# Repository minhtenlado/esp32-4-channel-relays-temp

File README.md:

<div align="center">

# ESP32-C3 MINI

### Bo mạch điều khiển IoT Wi-Fi & Bluetooth LE · 4 kênh relay · Cảm biến SHT31

**Bo mạch PCB 2 lớp được thiết kế bằng KiCad, tích hợp ESP32-C3, 4 ngõ ra relay, cảm biến nhiệt độ/độ ẩm SHT31, cổng USB Type-C và đầu mở rộng GPIO/UART.**

**[Giới thiệu](#-giới-thiệu) · [Hình ảnh PCB](#-hình-ảnh-pcb) · [Phần cứng](#-kiến-trúc-phần-cứng) · [Sơ đồ chân](#-bảng-phân-bổ-chân) · [Cấu trúc dự án](#-cấu-trúc-thư-mục) · [Hướng dẫn sử dụng](#-hướng-dẫn-sử-dụng)**

</div>

---

## 📖 Giới thiệu

**ESP32-C3 MINI** là bo mạch điều khiển IoT được thiết kế riêng, phục vụ các ứng dụng điều khiển thiết bị và giám sát môi trường. Trung tâm hệ thống là mô-đun **ESP32-C3-WROOM-02**, kết hợp **4 relay chuyển mạch SPDT** và cảm biến nhiệt độ, độ ẩm **Sensirion SHT31-DIS**.

Thiết kế phù hợp để phát triển các ứng dụng tự động hóa sử dụng Wi-Fi, thu thập dữ liệu cảm biến và điều khiển tải thông qua relay. Repository này tập trung vào **thiết kế phần cứng, PCB và các tệp phục vụ sản xuất**; chưa bao gồm mã nguồn firmware ứng dụng trong bộ dữ liệu đã cung cấp.

### ✨ Tính năng nổi bật

- **ESP32-C3-WROOM-02:** hỗ trợ Wi-Fi 2,4 GHz và Bluetooth Low Energy (BLE).
- **4 kênh relay SPDT:** mỗi kênh sử dụng PC817 và transistor MMBT3904 để điều khiển cuộn relay.
- **Đầu nối NO / COM / NC:** mỗi relay có một terminal 3 chân để đấu nối tải.
- **SHT31-DIS:** cảm biến đo nhiệt độ và độ ẩm, giao tiếp I²C.
- **USB Type-C:** cấp nguồn 5 V và kết nối các đường dữ liệu USB tích hợp trên ESP32-C3.
- **Hai nút BOOT và RESET:** hỗ trợ khởi động, nạp chương trình và kiểm thử.
- **Đầu mở rộng 2 × 4 chân:** đưa ra UART, GPIO0, GPIO1, nguồn 3,3 V, nguồn 5 V và GND.
- **Các linh kiện bảo vệ:** cầu chì đầu vào, linh kiện bảo vệ ESD USB, diode dập xung ngược cho cuộn relay và vị trí lắp MOV ở phía tiếp điểm.
- **PCB 2 lớp:** bố trí linh kiện SMD/THT, có hình ảnh mô phỏng 3D và vùng dành riêng cho anten Wi-Fi.
---

## 🖼️ Hình ảnh PCB

### Mô hình 3D

| Góc nhìn 3D số 1 | Góc nhìn 3D số 2 |
| :---: | :---: |
|  |  |

### Bố trí linh kiện và các lớp đồng

| Tổng quan các lớp PCB | Bố trí footprint |
| :---: | :---: |
|  |  |

| Lớp đồng mặt trước — F.Cu | Lớp đồng mặt sau — B.Cu |
| :---: | :---: |
|  |  |

---

## 🧩 Kiến trúc phần cứng

### System Block Diagram

```mermaid
flowchart TB
    USB["USB Type-C / 5 V Input"] --> PWR["F1 Fuse + SS14 Diode + 5 V Power Rail"]
    PWR --> LDO["AMS1117-3.3 Voltage Regulator"]
    LDO --> ESP["ESP32-C3-WROOM-02"]
    PWR --> RELAYPOWER["Relay Coil Power Supply"]
    USB <-->|"USB D+ / D−"| ESP
    ESP <-->|"I²C: SDA / SCL"| SHT["SHT31-DIS Temperature & Humidity Sensor"]
    ESP <-->|"UART + GPIO"| HDR["2 × 4 Expansion Header"]
    ESP --> DRV["4 × PC817 + MMBT3904 Relay Drivers"]
    DRV --> COILS["4 Relay Coils"]
    RELAYPOWER --> COILS
    COILS -. "Mechanical Actuation" .-> CONTACTS["4 × NO / COM / NC Output Terminals"]
    MOV["MOV Surge Protection"] --- CONTACTS
```

### Thông số kỹ thuật

| Thông số | Giá trị / thiết kế |
|---|---|
| Tên dự án | `ESP32_C3_MINI` |
| Vi điều khiển / mô-đun | Espressif `ESP32-C3-WROOM-02` |
| Kết nối không dây | Wi-Fi 2,4 GHz, Bluetooth LE (khả năng của mô-đun) |
| Số lớp PCB | 2 lớp đồng: `F.Cu` và `B.Cu` |
| Độ dày PCB khai báo | 1,6 mm |
| Kích thước bo mạch tham chiếu | Khoảng 88 × 89,5 mm theo file PCB được cung cấp |
| Nguồn đầu vào chính | USB Type-C, 5 V danh định |
| Nguồn logic | 3,3 V qua `AMS1117-3.3` |
| Số kênh relay | 4 kênh SPDT, footprint kiểu SANYOU SRD |
| Mạch kích relay | 4 × `PC817` và 4 × `MMBT3904` |
| Linh kiện bảo vệ relay | 4 × `1N4007` và 4 × MOV `07D471K` trong thiết kế |
| Cảm biến | `SHT31-DIS`, giao tiếp I²C |
| Giao tiếp nạp / phát triển | USB tích hợp ESP32-C3 và UART tại đầu mở rộng |
| Nút điều khiển | BOOT (`S1`), RESET (`S2`) |
| Đầu nối mở rộng | Header 2 × 4, bước chân 2,54 mm (`J5`) |
| Công cụ thiết kế | KiCad |

---

## 🔌 Bảng phân bổ chân

### GPIO trên ESP32-C3

| Chức năng | Chân ESP32-C3 | Tên tín hiệu / ghi chú |
|---|---|---|
| Điều khiển relay 1 | `GPIO3` | `RL1` |
| Điều khiển relay 2 | `GPIO4` | `RL2` |
| Điều khiển relay 3 | `GPIO5` | `RL3` |
| Điều khiển relay 4 | `GPIO6` | `RL4` |
| SHT31 SDA | `GPIO7` | `SDA` |
| SHT31 SCL | `GPIO10` | `SCL` |
| USB D− | `GPIO18` | `D-` |
| USB D+ | `GPIO19` | `D+` |
| UART RX | `GPIO20` | `RX` |
| UART TX | `GPIO21` | `TX` |
| Nút BOOT | `GPIO9` | `IO9` |
| GPIO mở rộng | `GPIO0` | `IO0` |
| GPIO mở rộng | `GPIO1` | `IO1` |

> **Lưu ý chân khởi động:** GPIO2, GPIO8 và GPIO9 là các chân *strapping* của ESP32-C3. Không được thiết kế mạch ngoại vi làm thay đổi trạng thái khởi động ngoài ý muốn.

### Đầu nối mở rộng J5

| Chân | Tín hiệu | Chân | Tín hiệu |
|:---:|---|:---:|---|
| 1 | GPIO0 (`IO0`) | 2 | GND |
| 3 | GPIO1 (`IO1`) | 4 | GND |
| 5 | UART RX (`GPIO20`) | 6 | +3,3 V |
| 7 | UART TX (`GPIO21`) | 8 | +5 V |

> [!WARNING]
> Chân GPIO ESP32-C3 sử dụng logic **3,3 V**, không được đưa trực tiếp tín hiệu 5 V vào GPIO. Kiểm tra chiều đánh số chân header và khả năng cấp dòng của nguồn trước khi kết nối mô-đun bên ngoài.

### Cảm biến nhiệt độ / độ ẩm SHT31

| Chức năng | Kết nối |
|---|---|
| SDA | GPIO7 |
| SCL | GPIO10 |
| Điện trở kéo lên SDA/SCL | 4,7 kΩ lên 3,3 V (`R25`, `R26`) |
| Địa chỉ I²C | `0x44` theo cấu hình ADDR ở mức thấp trong sơ đồ đã gửi |
| Nguồn | 3,3 V |

### Các kênh relay

| Kênh | Ký hiệu relay | Terminal đầu ra | Tiếp điểm |
|:---:|---|---|---|
| 1 | `K1` | `J1` | NO · COM · NC |
| 2 | `K2` | `J2` | NO · COM · NC |
| 3 | `K3` | `J3` | NO · COM · NC |
| 4 | `K4` | `J4` | NO · COM · NC |

Theo cách bố trí mạch kích trong sơ đồ đã cung cấp, GPIO mức **HIGH** để kích relay.
---

## ⚡ Nguồn cấp và bảo vệ

### Khối nguồn

Nguồn **5 V từ USB Type-C** đi qua cầu chì `F1` và diode Schottky `D1 (SS14)` tới đường nguồn 5 V của mạch. IC `AMS1117-3.3` tạo ra nguồn **3,3 V** cho khối ESP32-C3 và các phần tử logic.

Mạch có linh kiện `PRTR5V0U2X` hỗ trợ bảo vệ chống phóng tĩnh điện (ESD) trên đường USB.

### Khối điều khiển relay

Mỗi kênh gồm các thành phần chính:

1. Tín hiệu GPIO từ ESP32-C3.
2. Optocoupler `PC817`.
3. Transistor `MMBT3904` điều khiển cuộn relay.
4. Diode `1N4007` dập xung điện áp ngược khi ngắt cuộn dây.
5. LED hiển thị trạng thái và mạng điện trở đi kèm.
6. Terminal đấu nối tải với ba tiếp điểm NO, COM và NC.

Thiết kế có thêm bốn vị trí MOV `RV1`–`RV4` ở khu vực tiếp điểm relay.

> [!CAUTION]
> **An toàn điện:** PCB và file Gerber không phải chứng nhận an toàn điện. Nếu đóng cắt điện lưới 110/220/240 VAC, phải kiểm tra khoảng cách cách điện trong không khí (*clearance*), khoảng cách rò trên bề mặt (*creepage*), ranh giới đồng điện áp cao/thấp, cầu chì, đầu nối, vỏ bảo vệ, định mức relay và tiêu chuẩn áp dụng. **Không thử điện lưới trên bo chưa được kiểm định an toàn.** Nên thử nghiệm ban đầu với tải điện áp thấp có giới hạn dòng.
---

## 📁 Cấu trúc thư mục

Cấu trúc bên dưới dựa trên gói dự án KiCad đã được cung cấp:

```text
ESP32_C3_MINI/
├── README.md                         # Tài liệu giới thiệu dự án
├── ESP32_C3_MINI.kicad_pro           # Cấu hình dự án KiCad
├── ESP32_C3_MINI.kicad_sch           # Sơ đồ nguyên lý
├── ESP32_C3_MINI.kicad_pcb           # Thiết kế PCB
├── ESP32_C3_MINI.kicad_prl           # Trạng thái trình biên tập cục bộ (không bắt buộc)
├── schematic.pdf                     # Sơ đồ nguyên lý đã xuất PDF
├── Images/
│   ├── ALL_layers.png                # Tổng quan các lớp PCB
│   ├── F_cu.png                      # Lớp đồng mặt trước
│   ├── B_cu.png                      # Lớp đồng mặt sau
│   ├── footprint.png                 # Bố trí footprint
│   ├── board_3D(1).png               # Ảnh 3D góc 1
│   ├── board_3D(2).png               # Ảnh 3D góc 2
│   └── board_3D(3).png               # Ảnh 3D góc 3
├── production/
│   ├── ESP32_C3_MINI.zip             # Gerber và dữ liệu khoan xuất từ PCB
│   ├── bom.csv                       # Danh sách vật tư (BOM)
│   ├── positions.csv                 # Vị trí / góc xoay linh kiện
│   ├── designators.csv               # Danh sách mã tham chiếu linh kiện
│   └── netlist.ipc                   # Dữ liệu kết nối IPC-D-356
└── library/                          # Symbol, footprint và mô hình 3D tùy chỉnh
    ├── 0603WAF1002T5E/
    ├── 0603WAF5101T5E/
    ├── CC0603KRX7R9BB104/
    ├── CL10A105KB8NNNC/
    ├── TS-1187A-B-A-B/
    └── TYPE-C_16PIN_2MD__073_/
```

Thư mục `library/` chứa các tệp ký hiệu, footprint, mô hình STEP và hướng dẫn nhập thư viện từ nhà cung cấp; một số linh kiện khác sử dụng thư viện tiêu chuẩn của KiCad.

### Các tệp quan trọng

| Tệp | Xem trong repository |
|---|---|
| Sơ đồ nguyên lý PDF | [Xem sơ đồ](schematic.pdf) |
| Schematic KiCad | [`ESP32_C3_MINI.kicad_sch`](ESP32_C3_MINI.kicad_sch) |
| Bố trí PCB | [`ESP32_C3_MINI.kicad_pcb`](ESP32_C3_MINI.kicad_pcb) |
| Danh sách linh kiện BOM | [`production/bom.csv`](production/bom.csv) |
| Tọa độ đặt linh kiện | [`production/positions.csv`](production/positions.csv) |
| Gói Gerber/Drill | [`production/ESP32_C3_MINI.zip`](production/ESP32_C3_MINI.zip) |

---

## 🚀 Hướng dẫn sử dụng

### Bước 1 — Tải dự án về máy

Trên GitHub, chọn **Code → Download ZIP** để tải toàn bộ mã nguồn thiết kế. Hoặc sử dụng Git sau khi bạn đã tạo repository cho bo mạch này:

```bash
git clone https://github.com/minhtenlado/esp32-4-channel-relays-temp.git
cd esp32-4-channel-relays-temp
```
### Bước 2 — Mở project bằng KiCad

1. Cài đặt phiên bản KiCad tương thích với file `.kicad_pro`, `.kicad_sch` và `.kicad_pcb`.
2. Mở file **`ESP32_C3_MINI.kicad_pro`** bằng KiCad Project Manager.
3. Vào **Schematic Editor** để xem và chỉnh sửa sơ đồ nguyên lý.
4. Vào **PCB Editor** để xem và chỉnh sửa bo mạch.
5. Nếu thiếu symbol, footprint hoặc mô hình 3D, nhập từ thư mục `library/` thông qua **Manage Symbol Libraries / Manage Footprint Libraries** và cập nhật lại đường dẫn mô hình nếu cần.

### Bước 3 — Kiểm tra thiết kế trước khi sản xuất

1. Trong Schematic Editor, chạy **Electrical Rules Checker (ERC)**.
2. Chọn **Tools → Update PCB from Schematic (`F8`)** để cập nhật kết nối sang PCB.
3. Đổ đồng lại các vùng copper zone bằng phím **`B`**.
4. Chạy **Design Rules Checker (DRC)** để tìm lỗi kết nối, khoảng cách và quy tắc thiết kế.
5. Kiểm tra ánh xạ chân **cuộn relay / COM / NO / NC** theo đúng mã relay và datasheet thực tế.
6. Kiểm tra vùng anten, nguồn cấp, đường bảo vệ, biên dạng bo và khoảng cách cách điện nếu có tải điện áp cao.
7. Xuất lại **Gerber và Drill** sau mỗi lần hoàn thiện PCB. Tệp `production/` cũ không tự động cập nhật khi bạn chỉnh sửa bản vẽ.

### Bước 4 — Kiểm tra bo mạch sau khi lắp ráp

Sử dụng nguồn điện áp thấp có giới hạn dòng. Kiểm tra lần lượt:

- Nguồn 5 V, nguồn 3,3 V và dòng tiêu thụ khi khởi động.
- Nút BOOT, RESET và kết nối USB.
- Khả năng nhận cảm biến SHT31 qua I²C.
- Từng kênh relay với tải thử điện áp thấp.
- Trạng thái NO / COM / NC thực tế khi relay bật và tắt.

### Bước 5 — Phát triển firmware

Bạn có thể phát triển firmware bằng **ESP-IDF** hoặc công cụ tương thích ESP32-C3. USB tích hợp sử dụng `GPIO18 (D−)` và `GPIO19 (D+)`; UART sử dụng `GPIO20 (RX)` và `GPIO21 (TX)` được đưa ra header `J5`.

> **Lưu ý:** Bộ dự án được cung cấp chưa có mã nguồn firmware. Việc khởi tạo GPIO, điều khiển relay, đọc SHT31, cấu hình Wi-Fi hoặc các giao thức IoT cần được phát triển và kiểm thử riêng.

---

## 🏭 Sản xuất và lắp ráp PCB

Các tệp bên trong thư mục [`production/`](production/) được sử dụng để tham khảo và chuẩn bị đặt làm PCB:

| Tên tệp | Công dụng |
|---|---|
| `ESP32_C3_MINI.zip` | Bộ Gerber và tệp khoan cho nhà sản xuất |
| `bom.csv` | Danh sách linh kiện, giá trị và footprint |
| `positions.csv` | Tọa độ và góc xoay linh kiện phục vụ lắp ráp |
| `designators.csv` | Danh sách mã tham chiếu linh kiện |
| `netlist.ipc` | Dữ liệu kết nối để đối chiếu/kiểm tra |

**Trước khi đặt PCB:** Cần đảm bảo schematic, layout `.kicad_pcb`, BOM, file vị trí linh kiện, ảnh 3D và Gerber/Drill thuộc **cùng một phiên bản thiết kế cuối cùng**. Xác nhận đầy đủ mã linh kiện và thông số định mức với đơn vị sản xuất/lắp ráp.

---

## 💡 Ứng dụng đề xuất

- Bộ điều khiển đóng/ngắt các thiết bị **điện áp thấp** qua Wi-Fi.
- Hệ thống theo dõi nhiệt độ, độ ẩm và kích hoạt relay theo ngưỡng.
- Bo mạch học tập và nghiên cứu ESP32-C3, USB, I²C, UART và điều khiển relay.
- Nền tảng phát triển thiết bị IoT kết nối với phần mềm hoặc hệ thống bên ngoài.

Đây là **những ứng dụng có thể phát triển** từ thiết kế phần cứng, không phải khẳng định tất cả đã có firmware hoàn chỉnh.

---

## 📚 Tài liệu tham khảo

- [Espressif — ESP32-C3-WROOM-02 Datasheet](https://documentation.espressif.com/esp32-c3-wroom-02_datasheet_en.html)
- [Espressif — Hướng dẫn thiết kế phần cứng ESP32-C3](https://docs.espressif.com/projects/esp-hardware-design-guidelines/en/latest/esp32c3/index.html)
- [Sensirion — SHT3x-DIS Datasheet](https://sensirion.com/media/documents/213E6A3B/63A5A569/Datasheet_SHT3x_DIS.pdf)
- [Tài liệu KiCad](https://docs.kicad.org/)

---

## 👨‍💻 Tác giả

**[@minhtenlado](https://github.com/minhtenlado)**  
Thiết kế phần cứng và PCB — **ESP32-C3 MINI**.

> **Bản quyền:** Bộ tệp dự án đã cung cấp chưa có file `LICENSE`. Nếu muốn chia sẻ quyền sử dụng, chỉnh sửa và phân phối lại, hãy bổ sung giấy phép phù hợp trong repository.

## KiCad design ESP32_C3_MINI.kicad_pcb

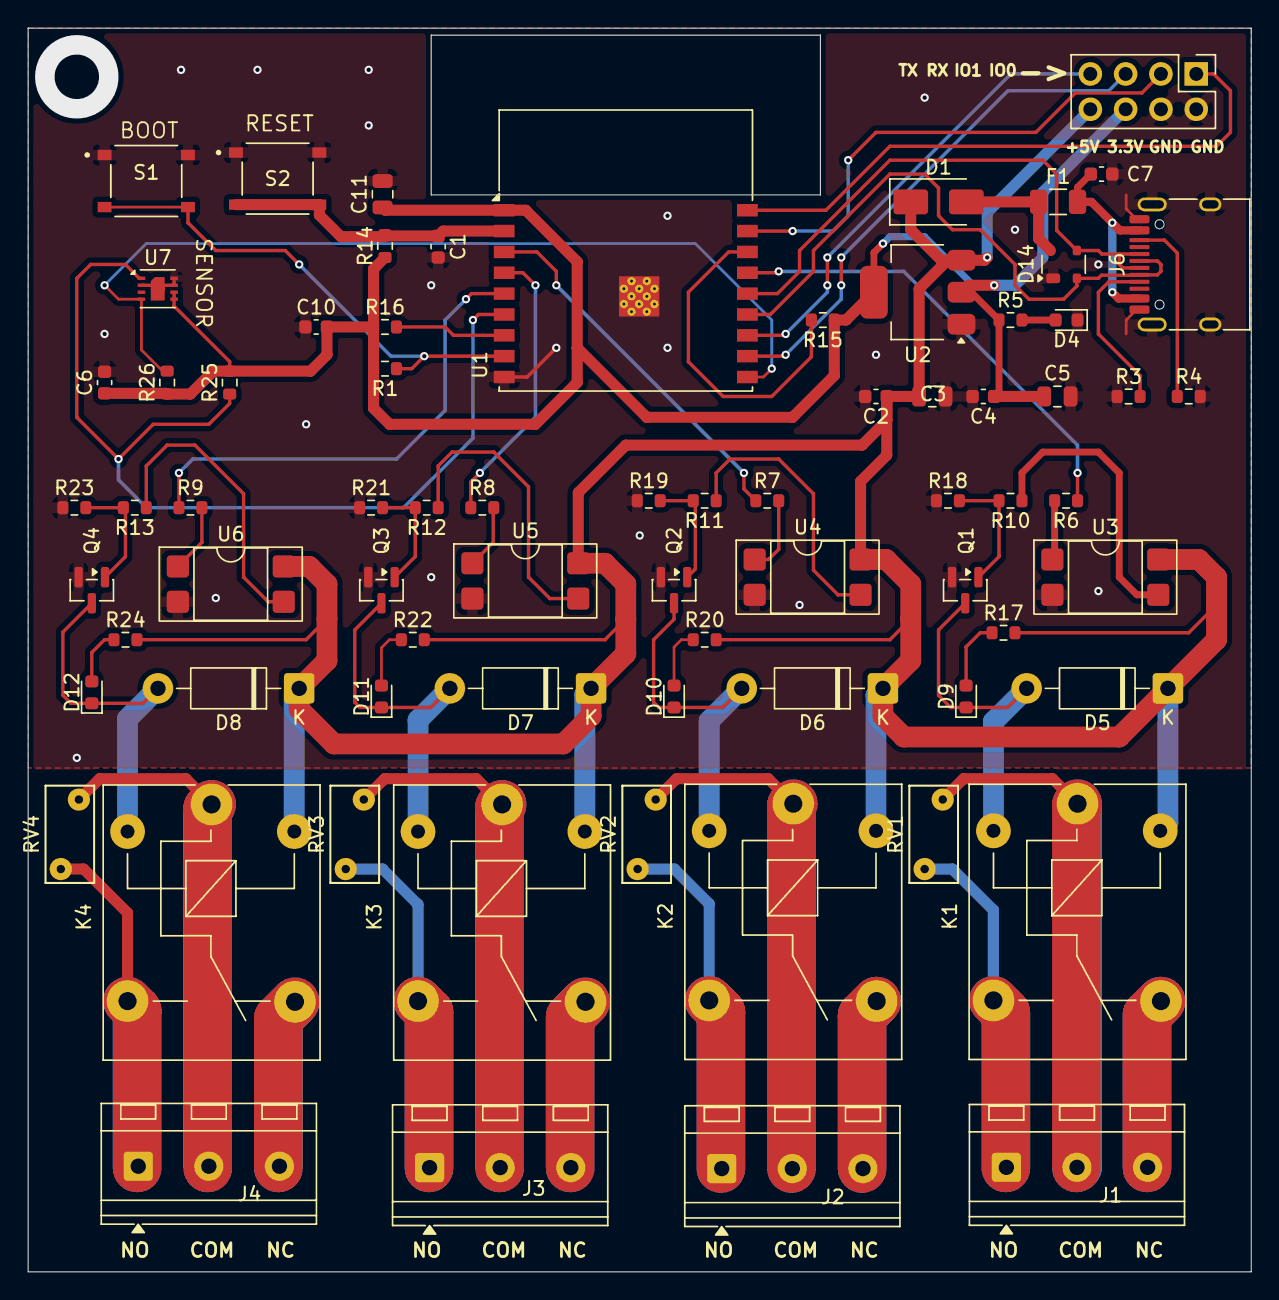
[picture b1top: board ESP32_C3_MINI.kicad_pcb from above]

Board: 2 copper layers, 88.0 x 89.5 mm, 74 parts (1 on the bottom side), 52 nets.

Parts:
C1: 1uF; C_0603_1608Metric
C2, C4, C6, C7, C10: 0.1uF; C_0603_1608Metric
C3, C5, C11: 10uF; C_0805_2012Metric
D1: SS14; D_SMA
D4: LED_G; LED_0603_1608Metric
D5, D6, D7, D8: 1N4007; D_DO-41_SOD81_P10.16mm_Horizontal
D9, D10, D11, D12: LED; LED_0603_1608Metric
D14: PRTR5V0U2X; SOT-143
F1: Fuse; Fuse_1206_3216Metric
J1, J2, J3, J4: Screw_Terminal_01x03; TerminalBlock_RND_205-00233_1x03_P5.08mm_Horizontal
J5: Conn_02x04_Odd_Even; PinHeader_2x04_P2.54mm_Vertical
J6: USB_C_Receptacle_USB2.0_16P; USB_C_Receptacle_HRO_TYPE-C-31-M-12
K1, K2, K3, K4: Relay_SPDT; Relay_SPDT_SANYOU_SRD_Series_Form_C
Q1, Q2, Q3, Q4: MMBT3904; SOT-23
QR*****: DESIGNER: Phan Huynh Van Do 08-Sep-2026 https://p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; Phan Huynh Van Do 08-Sep-2026 https_//phanhuynh.id.vn/
R1, R14, R15, R16, R18, R19, R21, R23: 10K; R_0603_1608Metric
R3, R4: 5.1K; R_0603_1608Metric
R5, R6, R7, R8, R9: 330; R_0603_1608Metric
R10, R11, R12, R13: 1K; R_0603_1608Metric
R17, R20, R22, R24: 680; R_0603_1608Metric
R25, R26: 4.7K; R_0603_1608Metric
RV1, RV2, RV3, RV4: 07D471K; RV_Disc_D7mm_W3.5mm_P5mm
S1, S2: TS-1187A-B-A-B; SW_TS-1187A-B-A-B
U1: ESP32-C3-WROOM-02
U2: AMS1117-3.3; SOT-223-3_TabPin2
U3, U4, U5, U6: PC817; DIP-4_W7.62mm_SMDSocket_SmallPads
U7: SHT31-DIS; Sensirion_DFN-8-1EP_2.5x2.5mm_P0.5mm_EP1.1x1.7mm

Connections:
/+3.3V: C4.1, C5.1, C6.1, C10.2, C11.1, J5.6, R1.2, R5.1, R14.1, R15.1, R16.1, R25.2, R26.1, U1.1 (3V3), U2.2 (VO), U7.5 (VDD), U7.6 (~RESET)
/+5V: C2.1, C3.1, D1.1 (K), D5.1 (K), D6.1 (K), D7.1 (K), D8.1 (K), J5.8, R17.2, R20.2, R22.2, R24.2, U2.3 (VI), U3.4, U4.4, U5.4, U6.4
/COM1: J1.2, RV1.1
/COM2: J2.2, RV2.1
/COM3: J3.2, RV3.1
/COM4: J4.2, RV4.1
/D+: D14.3 (I/O2), J6.A6 (D+), J6.B6 (D+), U1.14 (IO19)
/D-: D14.2 (I/O1), J6.A7 (D-), J6.B7 (D-), U1.13 (IO18)
/IO0: J5.1, U1.18 (IO0)
/IO1: J5.3, U1.17 (IO1)
/IO9: R1.1, S1.C, S1.D, U1.8 (IO9)
/NO2: J2.3, RV2.2
/RL1: R6.1, U1.15 (IO3)
/RL2: R7.1, U1.3 (IO4)
/RL3: R8.1, U1.4 (IO5)
/RL4: R9.1, U1.5 (IO6)
/RX: J5.5, U1.11 (IO20/RXD)
/SCL: R26.2, U1.10 (IO10), U7.4 (SCL)
/SDA: R25.1, U1.6 (IO7), U7.1 (SDA)
/TX: J5.7, U1.12 (IO21/TXD)
GND: C1.2, C2.2, C3.2, C4.2, C5.2, C6.2, C7.1, C10.1, C11.2, D4.1 (K), D14.1 (GND), J5.2, J5.4, J6.A1 (GND), J6.A12 (GND), J6.B1 (GND), J6.B12 (GND), J6.SH (SHIELD), Q1.2 (E), Q2.2 (E), Q3.2 (E), Q4.2 (E), R3.1, R4.2, R18.1, R19.1, R21.1, R23.1, S1.A, S1.B, S2.A, S2.B, U1.9 (GND), U1.19 (GND), U2.1 (GND), U3.2, U4.2, U5.2, U6.2, U7.2 (ADDR), U7.7 (R), U7.8 (VSS), U7.9 (VSS)
unnamed: C7.2, F1.2, J6.A4 (VBUS), J6.A9 (VBUS), J6.B4 (VBUS), J6.B9 (VBUS)
unnamed: D1.2 (A), D14.4 (VCC), F1.1
unnamed: D4.2 (A), R5.2
unnamed: D5.2 (A), D9.1 (K), Q1.3 (C)
unnamed: D9.2 (A), R17.1
unnamed: D10.2 (A), R20.1
unnamed: D6.2 (A), D10.1 (K), Q2.3 (C)
unnamed: D11.2 (A), R22.1
unnamed: D7.2 (A), D11.1 (K), Q3.3 (C)
unnamed: D12.2 (A), R24.1
unnamed: D8.2 (A), D12.1 (K), Q4.3 (C)
unnamed: J1.3, RV1.2
unnamed: J3.3, RV3.2
unnamed: J4.3, RV4.2
unnamed: J6.A5 (CC1), R3.2
unnamed: J6.B5 (CC2), R4.1
unnamed: Q1.1 (B), R10.2, R18.2
unnamed: Q2.1 (B), R11.2, R19.2
unnamed: Q3.1 (B), R12.2, R21.2
unnamed: Q4.1 (B), R13.2, R23.2
unnamed: R6.2, U3.1
unnamed: R7.2, U4.1
unnamed: R8.2, U5.1
unnamed: R9.2, U6.1
unnamed: R10.1, U3.3
unnamed: R11.1, U4.3
unnamed: R12.1, U5.3
unnamed: R13.1, U6.3
unnamed: C1.1, R14.2, S2.C, S2.D, U1.2 (EN)
unnamed: R15.2, U1.16 (IO2)
unnamed: R16.2, U1.7 (IO8)

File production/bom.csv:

Designator,Footprint,Quantity,Value,LCSC Part #
C1,0603,1,1uF,
"C10, C2, C4, C6, C7",0603,5,0.1uF,
"C11, C3, C5",0805,3,10uF,
D1,D_SMA,1,SS14,
"D10, D11, D12, D9",0603,4,LED,
D14,SOT-143,1,PRTR5V0U2X,
D4,0603,1,LED_G,
"D5, D6, D7, D8",D_DO-41_SOD81_P10.16mm_Horizontal,4,1N4007,
F1,1206,1,Fuse,
"J1, J2, J3, J4",TerminalBlock_RND_205-00233_1x03_P5.08mm_Horizontal,4,Screw_Terminal_01x03,
J5,PinHeader_2x04_P2.54mm_Vertical,1,Conn_02x04_Odd_Even,
J6,USB_C_Receptacle_HRO_TYPE-C-31-M-12,1,USB_C_Receptacle_USB2.0_16P,
"K1, K2, K3, K4",Relay_SPDT_SANYOU_SRD_Series_Form_C,4,Relay_SPDT,
"Q1, Q2, Q3, Q4",SOT-23,4,MMBT3904,
"R1, R14, R15, R16, R18, R19, R21, R23",0603,8,10K,
"R10, R11, R12, R13",0603,4,1K,
"R17, R20, R22, R24",0603,4,680,
"R25, R26",0603,2,4.7K,
"R3, R4",0603,2,5.1K,
"R5, R6, R7, R8, R9",0603,5,330,
"RV1, RV2, RV3, RV4",RV_Disc_D7mm_W3.5mm_P5mm,4,07D471K,
"S1, S2",SW_TS-1187A-B-A-B,2,TS-1187A-B-A-B,
U1,ESP32-C3-WROOM-02,1,ESP32-C3-WROOM-02,
U2,SOT-223-3_TabPin2,1,AMS1117-3.3,
"U3, U4, U5, U6",DIP-4_W7.62mm_SMDSocket_SmallPads,4,PC817,
U7,Sensirion_DFN-8-1EP_2.5x2.5mm_P0.5mm_EP1.1x1.7mm,1,SHT31-DIS,

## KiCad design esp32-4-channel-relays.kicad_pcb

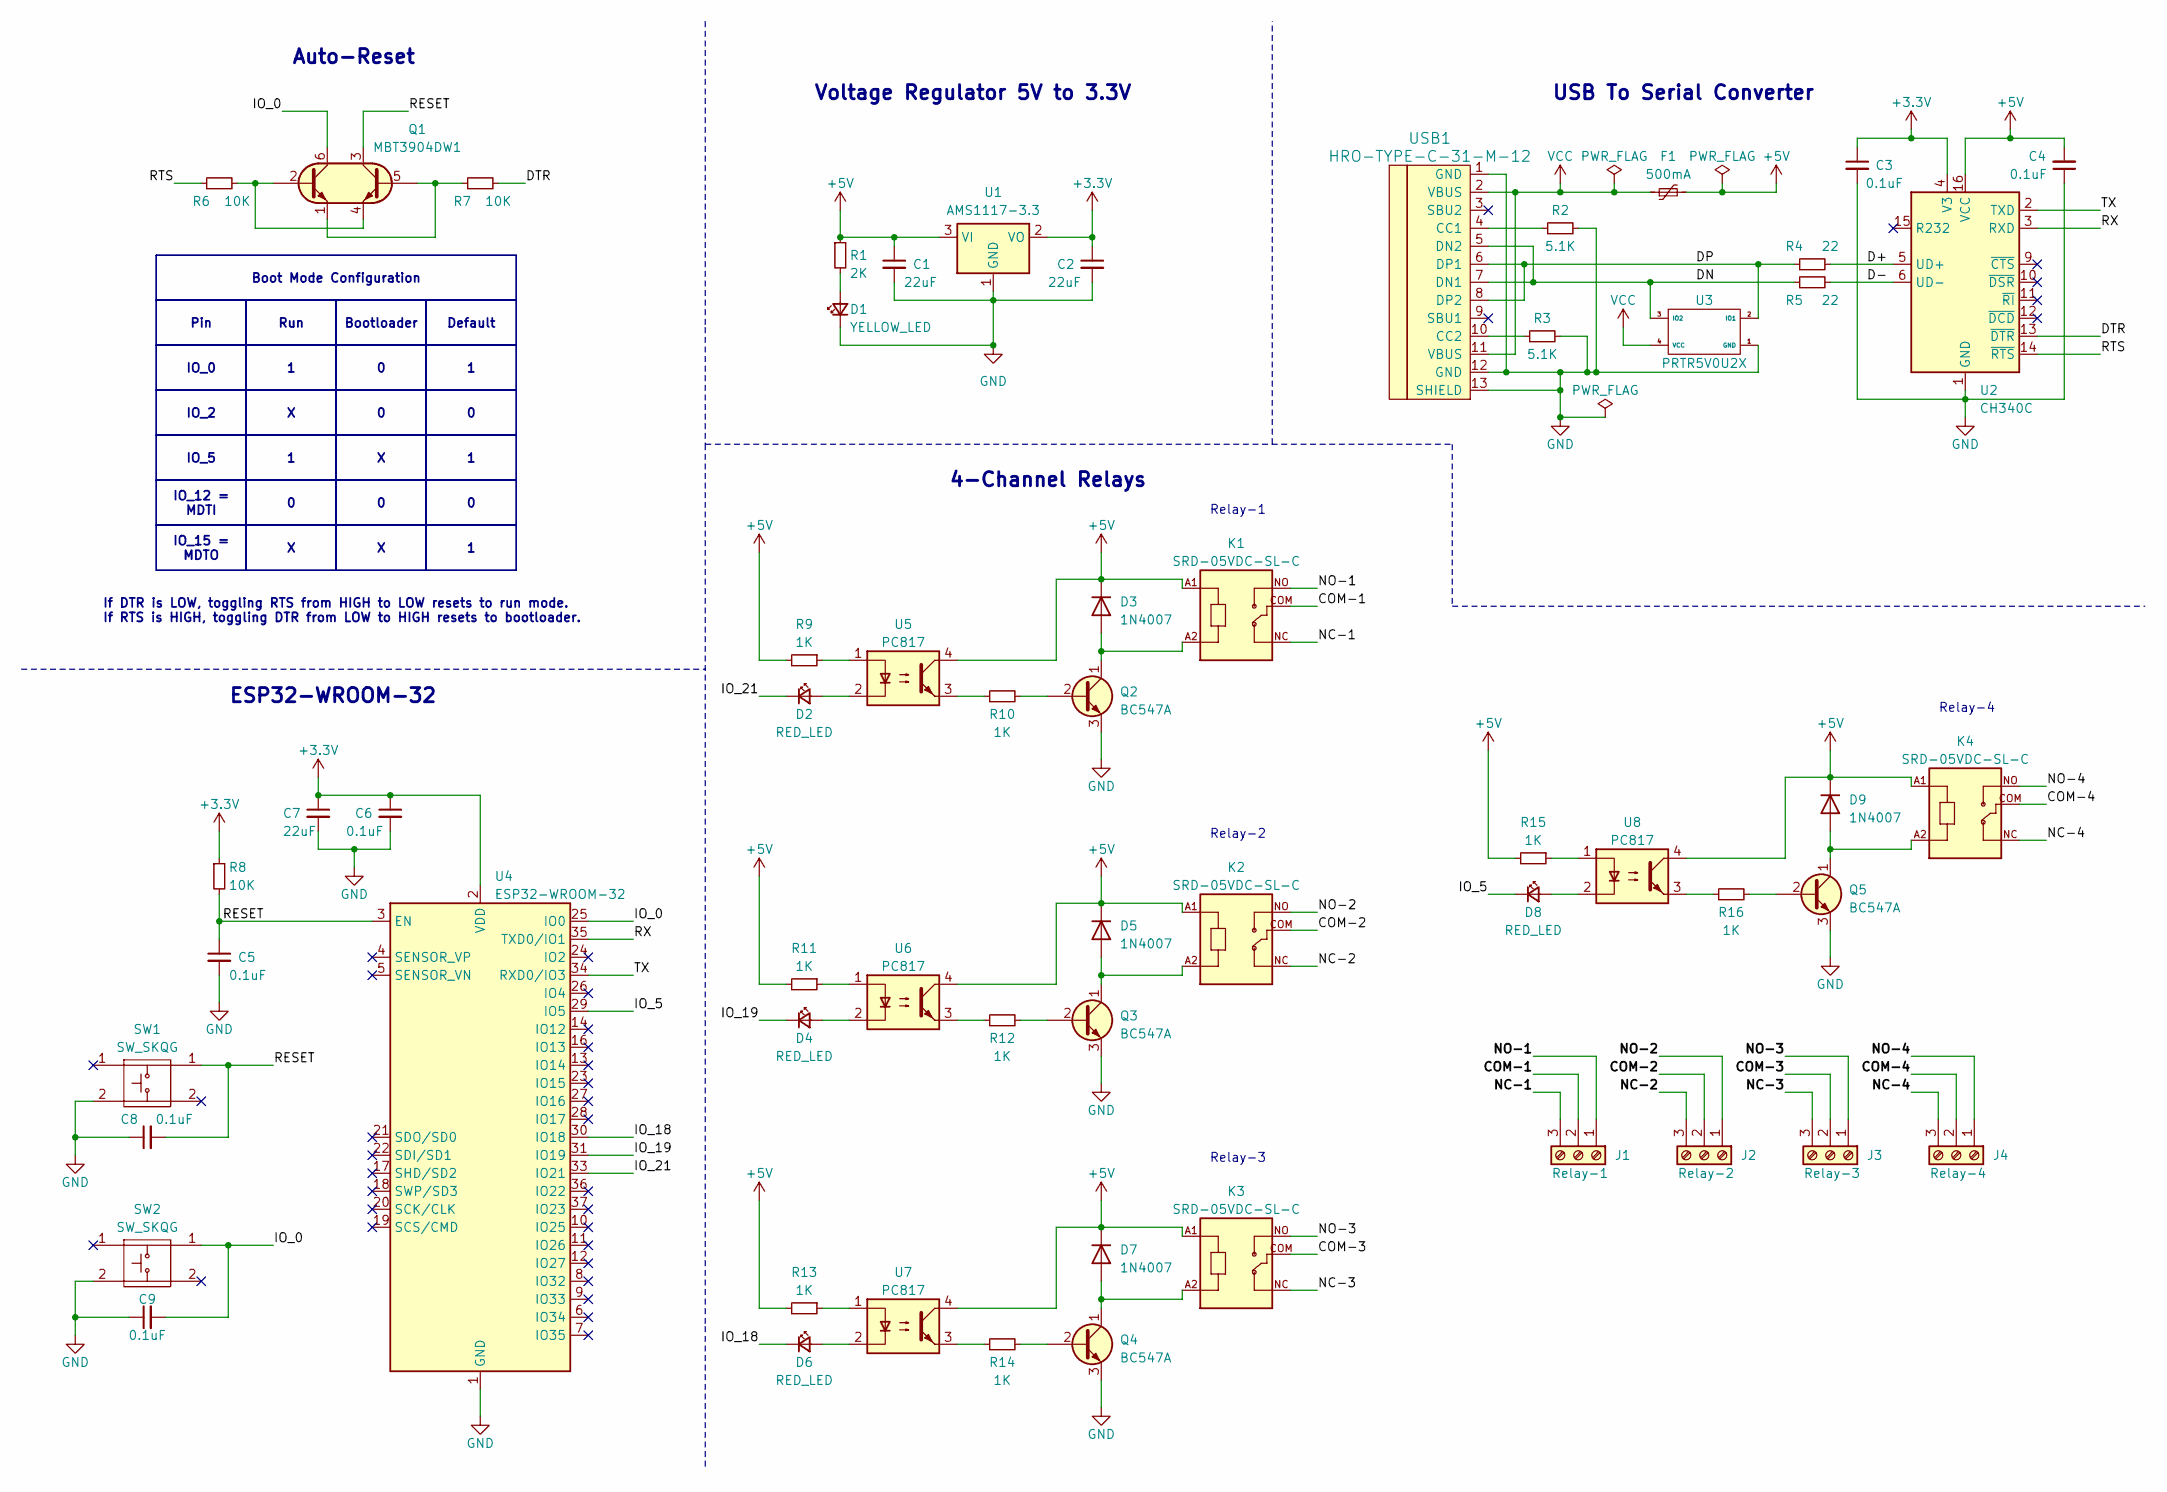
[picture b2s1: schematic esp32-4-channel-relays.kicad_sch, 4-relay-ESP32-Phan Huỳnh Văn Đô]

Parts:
C1, C2, C7: 22uF; C_0805_2012Metric_Pad1.18x1.45mm_HandSolder
C3, C4, C5, C6, C8, C9: 0.1uF; C_0805_2012Metric_Pad1.18x1.45mm_HandSolder
D1: YELLOW_LED; LED_0805_2012Metric_Pad1.15x1.40mm_HandSolder
D2, D4, D6, D8: RED_LED; LED_0805_2012Metric_Pad1.15x1.40mm_HandSolder
D3, D5, D7, D9: 1N4007; D_MELF_Handsoldering
F1: 500mA; Fuse_1206_3216Metric_Pad1.42x1.75mm_HandSolder
J1: Relay-1; TerminalBlock_Phoenix_MKDS-1,5-3-5.08_1x03_P5.08mm_Horizont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
J2: Relay-2; TerminalBlock_Phoenix_MKDS-1,5-3-5.08_1x03_P5.08mm_Horizont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
J3: Relay-3; TerminalBlock_Phoenix_MKDS-1,5-3-5.08_1x03_P5.08mm_Horizont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
J4: Relay-4; TerminalBlock_Phoenix_MKDS-1,5-3-5.08_1x03_P5.08mm_Horizont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
K1, K2, K3, K4: SRD-05VDC-SL-C; RELAY_SRD-05VDC-SL-C
Q1: MBT3904DW1; SOT-363_SC-70-6_Handsoldering
Q2, Q3, Q4, Q5: BC547A; TSOT-23_HandSoldering
R1: 2K; R_0805_2012Metric_Pad1.20x1.40mm_HandSolder
R2, R3: 5.1K; R_0805_2012Metric_Pad1.20x1.40mm_HandSolder
R4, R5: 22; R_0805_2012Metric_Pad1.20x1.40mm_HandSolder
R6, R7, R8: 10K; R_0805_2012Metric_Pad1.20x1.40mm_HandSolder
R9, R10, R11, R12, R13, R14, R15, R16: 1K; R_0805_2012Metric_Pad1.20x1.40mm_HandSolder
SW1, SW2: SW_SKQG; SW_SPST_SKQG_WithStem
U1: AMS1117-3.3; SOT-223-3_TabPin2
U2: CH340C; SOIC-16_3.9x9.9mm_P1.27mm
U3: PRTR5V0U2X; SOT-143_Handsoldering
U4: ESP32-WROOM-32
U5, U6, U7, U8: PC817; SMDIP-4_W7.62mm
USB1: HRO-TYPE-C-31-M-12; HRO-TYPE-C-31-M-12-HandSoldering

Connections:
+3.3V: C2.1, C3.1, C6.1, C7.1, R8.1, U1.2 (VO), U2.4 (V3), U4.2 (VDD)
+5V: C1.1, C4.2, D3.1 (K), D5.1 (K), D7.1 (K), D9.1 (K), F1.2, K1.A1, K2.A1, K3.A1, K4.A1, R1.1, R9.2, R11.2, R13.2, R15.2, U1.3 (VI), U2.16 (VCC), U5.4, U6.4, U7.4, U8.4
/COM-1: J1.2, K1.COM
/COM-2: J2.2, K2.COM
/COM-3: J3.2, K3.COM
/COM-4: J4.2, K4.COM
/D+: R4.2, U2.5 (UD+)
/D-: R5.2, U2.6 (UD-)
/DN: R5.1, U3.3 (IO2), USB1.5 (DN2), USB1.7 (DN1)
/DP: R4.1, U3.2 (IO1), USB1.6 (DP1), USB1.8 (DP2)
/DTR: R7.2, U2.13 (~DTR)
/IO_0: C9.2, Q1.6 (C1), SW2.1, U4.25 (IO0)
/IO_5: D8.1 (K), U4.29 (IO5)
/IO_18: D6.1 (K), U4.30 (IO18)
/IO_19: D4.1 (K), U4.31 (IO19)
/IO_21: D2.1 (K), U4.33 (IO21)
/NC-1: J1.3, K1.NC
/NC-2: J2.3, K2.NC
/NC-3: J3.3, K3.NC
/NC-4: J4.3, K4.NC
/NO-1: J1.1, K1.NO
/NO-2: J2.1, K2.NO
/NO-3: J3.1, K3.NO
/NO-4: J4.1, K4.NO
/RESET: C5.1, C8.2, Q1.3 (C2), R8.2, SW1.1, U4.3 (EN)
/RTS: R6.1, U2.14 (~RTS)
/RX: U2.3 (RXD), U4.35 (TXD0/IO1)
/TX: U2.2 (TXD), U4.34 (RXD0/IO3)
GND: C1.2, C2.2, C3.2, C4.1, C5.2, C6.2, C7.2, C8.1, C9.1, D1.1 (K), Q2.3 (E), Q3.3 (E), Q4.3 (E), Q5.3 (E), R2.2, R3.2, SW1.2, SW2.2, U1.1 (GND), U2.1 (GND), U3.1 (GND), U4.1 (GND), U4.15 (GND), U4.38 (GND), U4.39 (GND), USB1.1 (GND), USB1.12 (GND), USB1.13 (SHIELD)
unnamed: D1.2 (A), R1.2
unnamed: D2.2 (A), U5.2
unnamed: D3.2 (A), K1.A2, Q2.1 (C)
unnamed: D4.2 (A), U6.2
unnamed: D5.2 (A), K2.A2, Q3.1 (C)
unnamed: D6.2 (A), U7.2
unnamed: D7.2 (A), K3.A2, Q4.1 (C)
unnamed: D8.2 (A), U8.2
unnamed: D9.2 (A), K4.A2, Q5.1 (C)
unnamed: Q1.2 (B1), Q1.4 (E2), R6.2
unnamed: Q1.1 (E1), Q1.5 (B2), R7.1
unnamed: Q2.2 (B), R10.2
unnamed: Q3.2 (B), R12.2
unnamed: Q4.2 (B), R14.2
unnamed: Q5.2 (B), R16.2
unnamed: R9.1, U5.1
unnamed: R10.1, U5.3
unnamed: R11.1, U6.1
unnamed: R12.1, U6.3
unnamed: R13.1, U7.1
unnamed: R14.1, U7.3
unnamed: R15.1, U8.1
unnamed: R16.1, U8.3
unnamed: R2.1, USB1.4 (CC1)
unnamed: R3.1, USB1.10 (CC2)
VCC: F1.1, U3.4 (VCC), USB1.2 (VBUS), USB1.11 (VBUS)

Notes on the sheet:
Voltage Regulator 5V to 3.3V
4-Channel Relays
Relay-1
Relay-4
Relay-3
Relay-2
Auto-Reset
ESP32-WROOM-32
If DTR is LOW, toggling RTS from HIGH to LOW resets to run mode. If RTS is HIGH, toggling DTR from LOW to HIGH resets to bootloader.
USB To Serial Converter
Default
IO_2
IO_15 = MDTO
Bootloader
IO_0
IO_12 = MDTI
Run
Boot Mode Configuration
IO_5
Pin

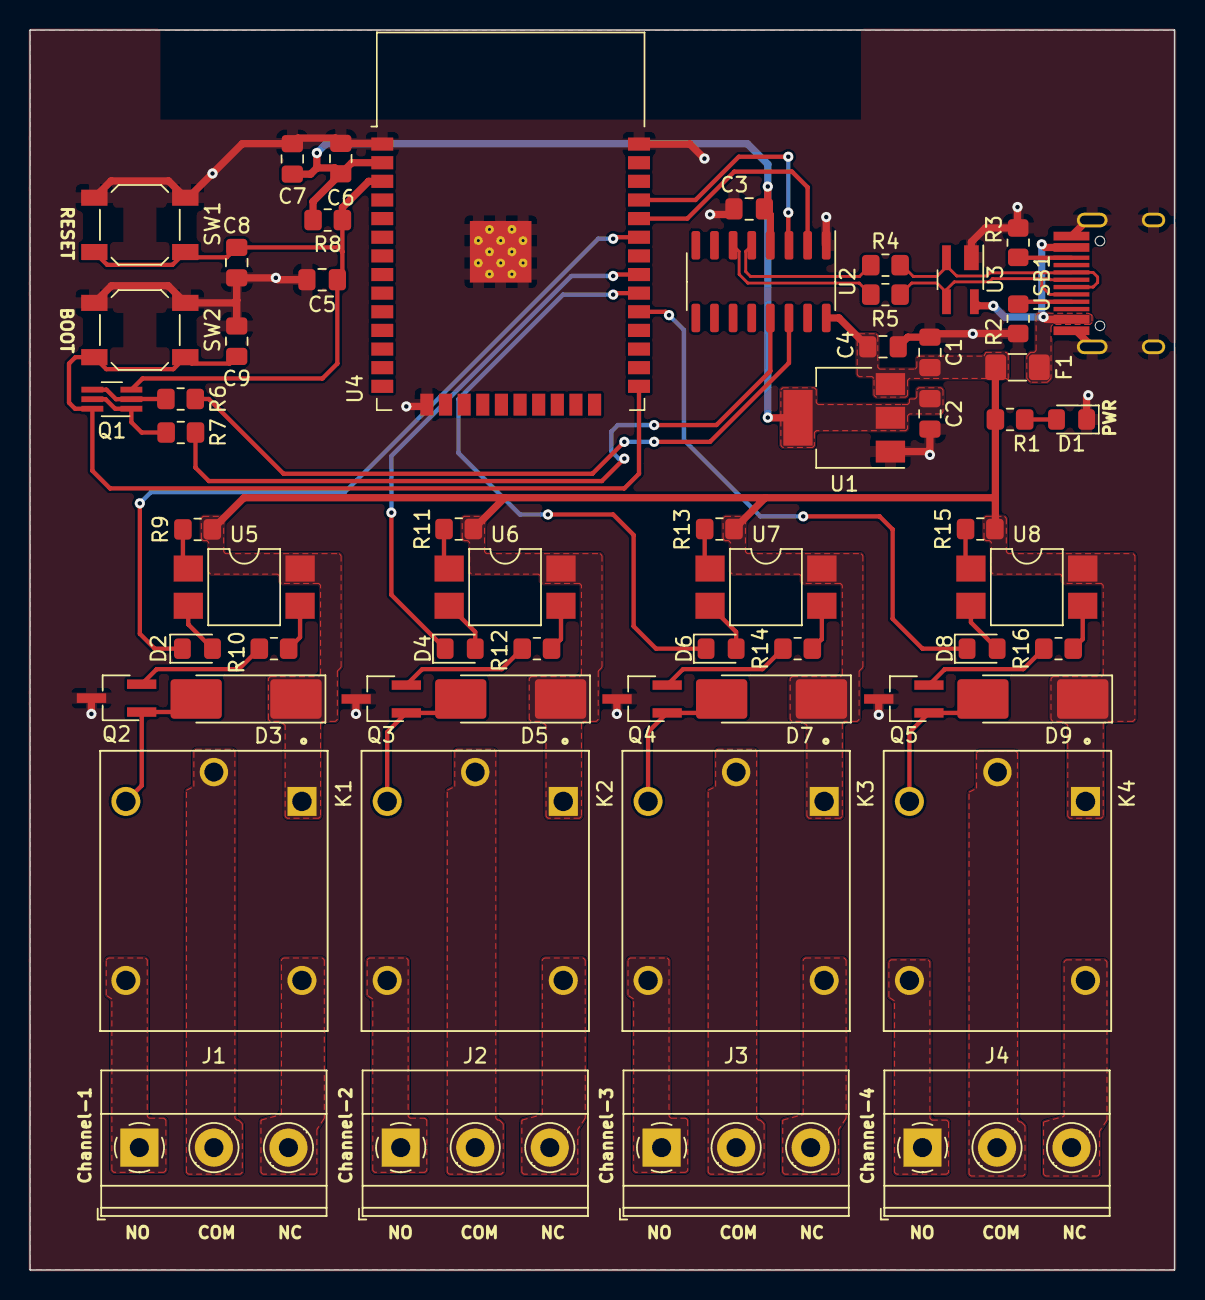
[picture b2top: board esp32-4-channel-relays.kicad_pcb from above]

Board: 2 copper layers, 78.0 x 84.5 mm, 59 parts (0 on the bottom side), 55 nets.

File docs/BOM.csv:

Item,Qty,Reference,Value,Footprint,Description
1,1,U4,ESP32-WROOM-32,Module SMD,Wi-Fi & Bluetooth Dual-Core MCU Module
2,4,"K1, K2, K3, K4",SRD-05VDC-SL-C,THT Relay,5VDC SPDT Relay (10A 250VAC / 10A 30VDC)
3,4,"U5, U6, U7, U8",PC817,SMDIP-4,Optocoupler Phototransistor Galvanic Isolator
4,4,"Q2, Q3, Q4, Q5",BC547A / NPN,SOT-23,NPN General Purpose Transistor (Relay Coil Driver)
5,4,"D3, D5, D7, D9",1N4007,MELF / DO-213AB,1A 1000V General Purpose Flyback Diode
6,4,"D2, D4, D6, D8",RED LED,0805 SMD,Relay Channel 1-4 Active Status Indicator
7,1,D1,YELLOW LED,0805 SMD,3.3V Power Rail Indicator
8,4,"J1, J2, J3, J4",Screw Terminal 3-Pin,5.08mm Pitch,"Screw Terminal (NO, COM, NC Contacts)"
9,1,USB1,Type-C 16-Pin,HRO-TYPE-C-31-M-12,USB Type-C Receptacle 5V Power & Data
10,1,U2,CH340C,SOIC-16,USB to Serial UART Interface with Built-in Oscillator
11,1,Q1,MBT3904DW1,SOT-363 / SC-70-6,Dual NPN Transistor Auto-Reset & Download Circuit
12,1,U1,AMS1117-3.3,SOT-223-3,3.3V 1A Low Dropout Linear Voltage Regulator
13,1,U3,PRTR5V0U2X,SOT-143,Ultra-low Capacitance TVS Diode ESD Protection
14,1,F1,500mA PTC,1206 SMD,Resettable Polyfuse Overcurrent Protection
15,2,"SW1, SW2",Tactile Button,SKQG / 6x6mm SMD,Tactile Switches (RESET / BOOT)
16,8,"R9, R10, R11, R12, R13, R14, R15, R16",1kΩ 1%,0805 SMD,Optocoupler LED Current Limiting & Base Drive Resistors
17,3,"R6, R7, R8",10kΩ 1%,0805 SMD,Pull-Up Resistors (EN / IO0 / BOOT)
18,2,"R2, R3",5.1kΩ 1%,0805 SMD,USB Type-C CC1 / CC2 Pull-Down Resistors
19,2,"R4, R5",22Ω 1%,0805 SMD,USB D+ / D- Series Termination Resistors
20,1,R1,2kΩ 1%,0805 SMD,Power LED Current Limiting Resistor
21,3,"C1, C2, C7",22µF 16V,0805 SMD,Bulk Filtering Capacitors (5V / 3.3V rails)
22,6,"C3, C4, C5, C6, C8, C9",0.1µF (100nF) 50V,0805 SMD,Decoupling Ceramic Capacitors
